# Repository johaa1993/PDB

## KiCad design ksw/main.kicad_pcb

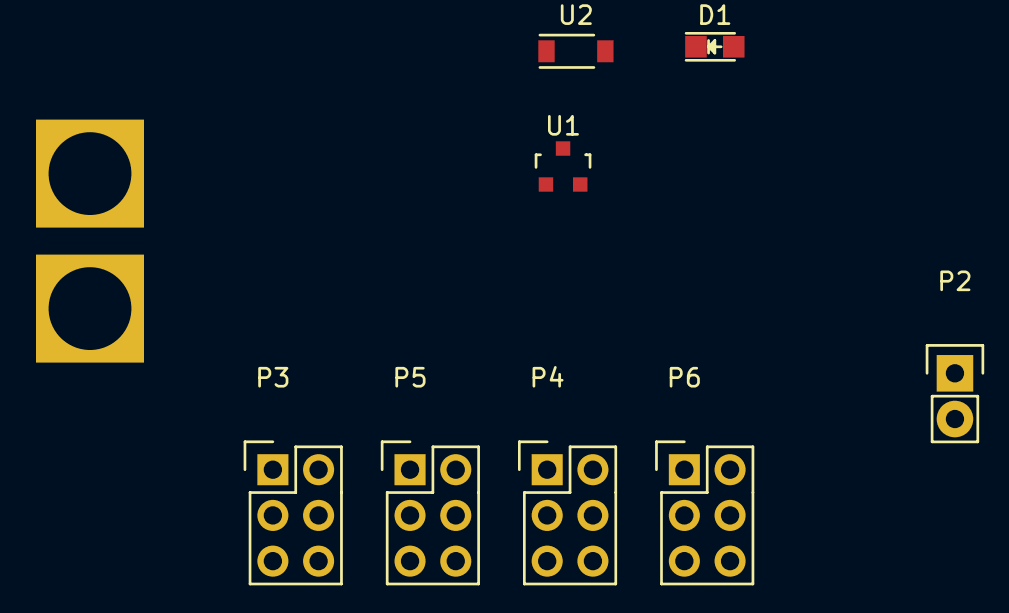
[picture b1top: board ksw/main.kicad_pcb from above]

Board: 2 copper layers, 9 parts (0 on the bottom side), 5 nets, no tracks yet.

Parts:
D1: 3.3v; LED_0805
P1: CONN_XT60; XT60
P2: CONN_01X02; Pin_Header_Straight_1x02
P3, P4, P5, P6: CONN_02X03; Pin_Header_Straight_2x03
U1: LM3480-3.3; SOT-23
U2: NSI45020AT1G; SOD-123

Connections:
+3V3: P3.6, P4.6, P5.6, P6.6, U1.1
/GND: D1.1, P1.1, P3.1, P4.1, P5.1, P6.1, U1.3
/In+: P1.2, U1.2, U2.2
unnamed: D1.2, P2.2, U2.1
unnamed: P2.1, P3.5, P4.5, P5.5, P6.5

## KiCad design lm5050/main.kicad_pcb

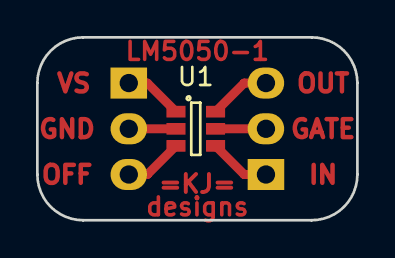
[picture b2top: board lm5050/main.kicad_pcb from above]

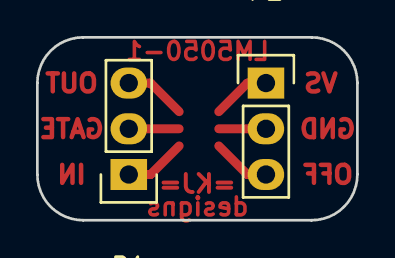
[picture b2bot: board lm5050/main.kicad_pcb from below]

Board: 2 copper layers, 17.8 x 10.2 mm, 3 parts (2 on the bottom side), 6 nets.

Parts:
P1, P2: CONN_01X03; Pin_Header_Straight_1x03
U1: LM5050; SOT-23-6

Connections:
unnamed: P1.1, U1.4
unnamed: P1.2, U1.5
unnamed: P1.3, U1.6
unnamed: P2.1, U1.1
unnamed: P2.2, U1.2
unnamed: P2.3, U1.3

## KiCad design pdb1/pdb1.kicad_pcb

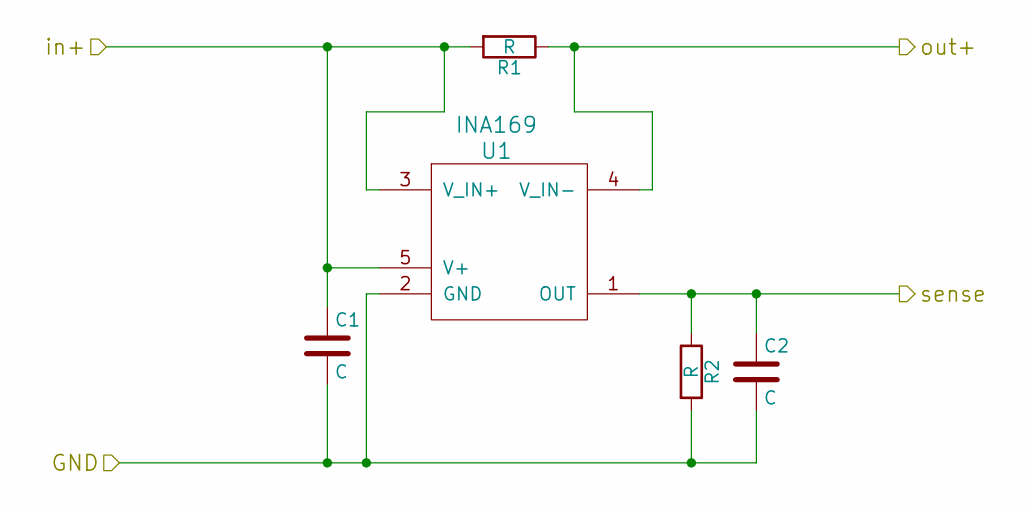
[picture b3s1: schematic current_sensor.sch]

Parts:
C1, C2: C; C_0603
R1: R; SMD_1052_Metric
R2: R; R_0603
U1: INA169; SOT-23-5

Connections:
/channel/GND: C1.2, C2.2, R2.2, U1.2 (GND); also elsewhere on the board
/channel/current_sensor/sense: C2.1, R2.1, U1.1 (OUT); also elsewhere on the board
/channel/fuse/in+: R1.1, U1.4 (V_IN-); also elsewhere on the board
/channel/in+: C1.1, R1.2, U1.3 (V_IN+), U1.5 (V+); also elsewhere on the board

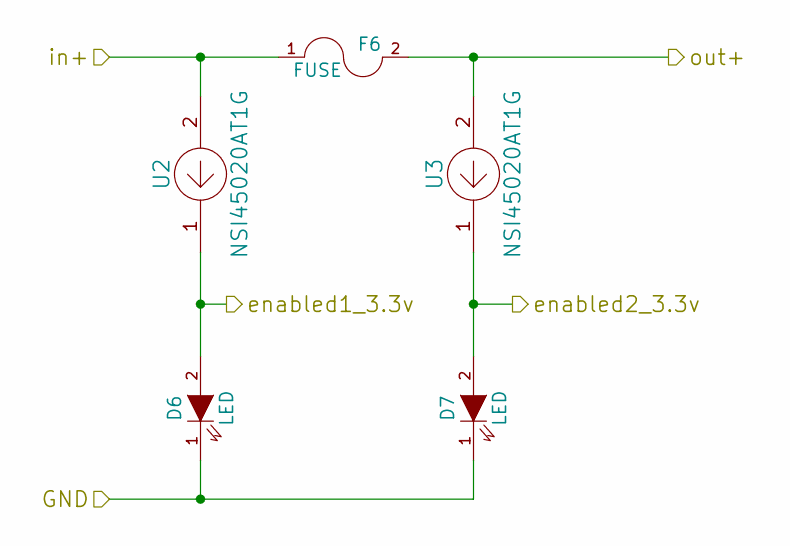
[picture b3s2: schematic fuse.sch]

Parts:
D6, D7: LED; LED_0805
F6: FUSE; Fuseholder_test
U2, U3: NSI45020AT1G; SOD-123

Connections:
/channel/GND: D6.1 (K), D7.1 (K); also elsewhere on the board
/channel/fuse/enabled1_3.3v: D6.2 (A), U2.1; also elsewhere on the board
/channel/fuse/enabled2_3.3v: D7.2 (A), U3.1; also elsewhere on the board
/channel/fuse/in+: F6.1, U2.2; also elsewhere on the board
/channel/kill_sw/in+: F6.2, U3.2; also elsewhere on the board

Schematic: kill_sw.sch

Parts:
C3: CP; C_Radial_D5_L6_P2.5
D9: LED; LED_0805
P4, P5: CONN_01X02; Pin_Header_Straight_1x02
Q2: BUK9Y4R8-60E; SOT-669_LFPAK
R3, R4: R; R_0603
U4: LM3480-3.3; SOT-23
U5: 74LVC1G08; SOT-353
U7: MIC5014; SOIC-8_3.9x4.9mm_Pitch1.27mm
U8: NSI45020AT1G; SOD-123

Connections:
/channel/GND: C3.2, D9.1 (K), R3.2, R4.2, U4.3, U5.3, U7.4 (Gnd); also elsewhere on the board
/channel/kill_sw/enable: P5.1, R3.1, U5.2; also elsewhere on the board
/channel/kill_sw/enabled2_3.3v: D9.2 (A), U8.1; also elsewhere on the board
/channel/kill_sw/in+: C3.1, Q2.5 (D), U4.2, U7.1 (V+); also elsewhere on the board
/channel/out+: Q2.1 (S), Q2.2 (S), Q2.3 (S), U7.3 (Source), U8.2; also elsewhere on the board
unnamed: P4.1, U4.1, U5.5
unnamed: P4.2, P5.2, R4.1, U5.1
unnamed: Q2.4 (G), U7.5 (Gate)
unnamed: U5.4, U7.2 (Input)

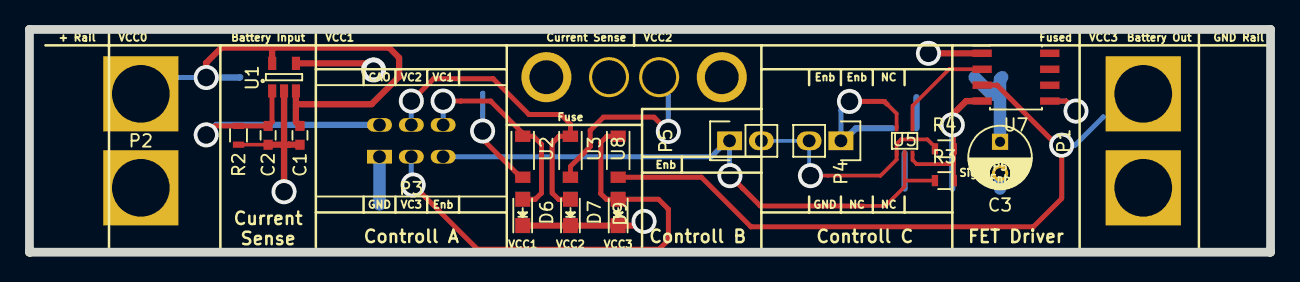
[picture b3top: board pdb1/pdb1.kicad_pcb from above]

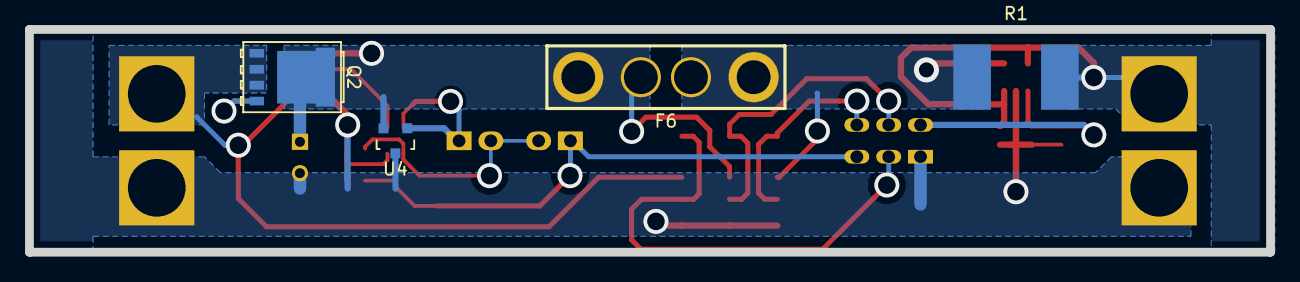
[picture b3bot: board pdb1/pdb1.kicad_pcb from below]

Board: 2 copper layers, 99.1 x 17.8 mm, 24 parts (4 on the bottom side), 14 nets.

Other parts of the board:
P1, P2: CONN_XT60; XT60
P3: CONN_02X03; Pin_Header_Straight_2x03_box

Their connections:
/channel/GND: P1.1, P2.1, P3.1; also elsewhere on the board
/channel/current_sensor/sense: P3.2; also elsewhere on the board
/channel/fuse/enabled1_3.3v: P3.6; also elsewhere on the board
/channel/fuse/enabled2_3.3v: P3.4; also elsewhere on the board
/channel/in+: P2.2; also elsewhere on the board
/channel/kill_sw/enable: P3.5; also elsewhere on the board
/channel/kill_sw/enabled2_3.3v: P3.3; also elsewhere on the board
/channel/out+: P1.2; also elsewhere on the board

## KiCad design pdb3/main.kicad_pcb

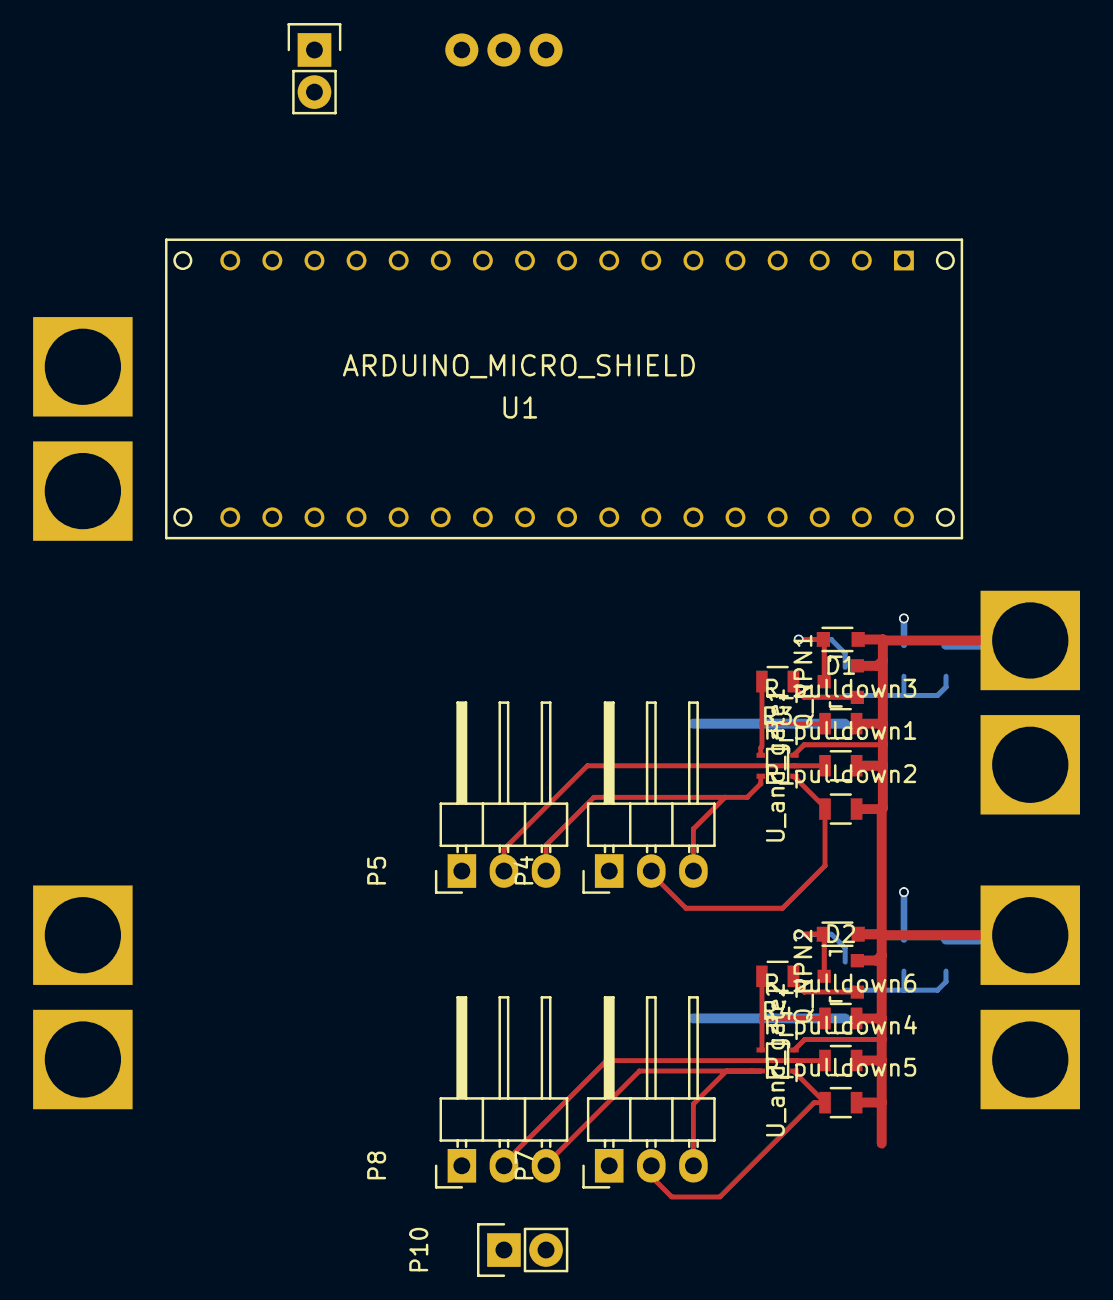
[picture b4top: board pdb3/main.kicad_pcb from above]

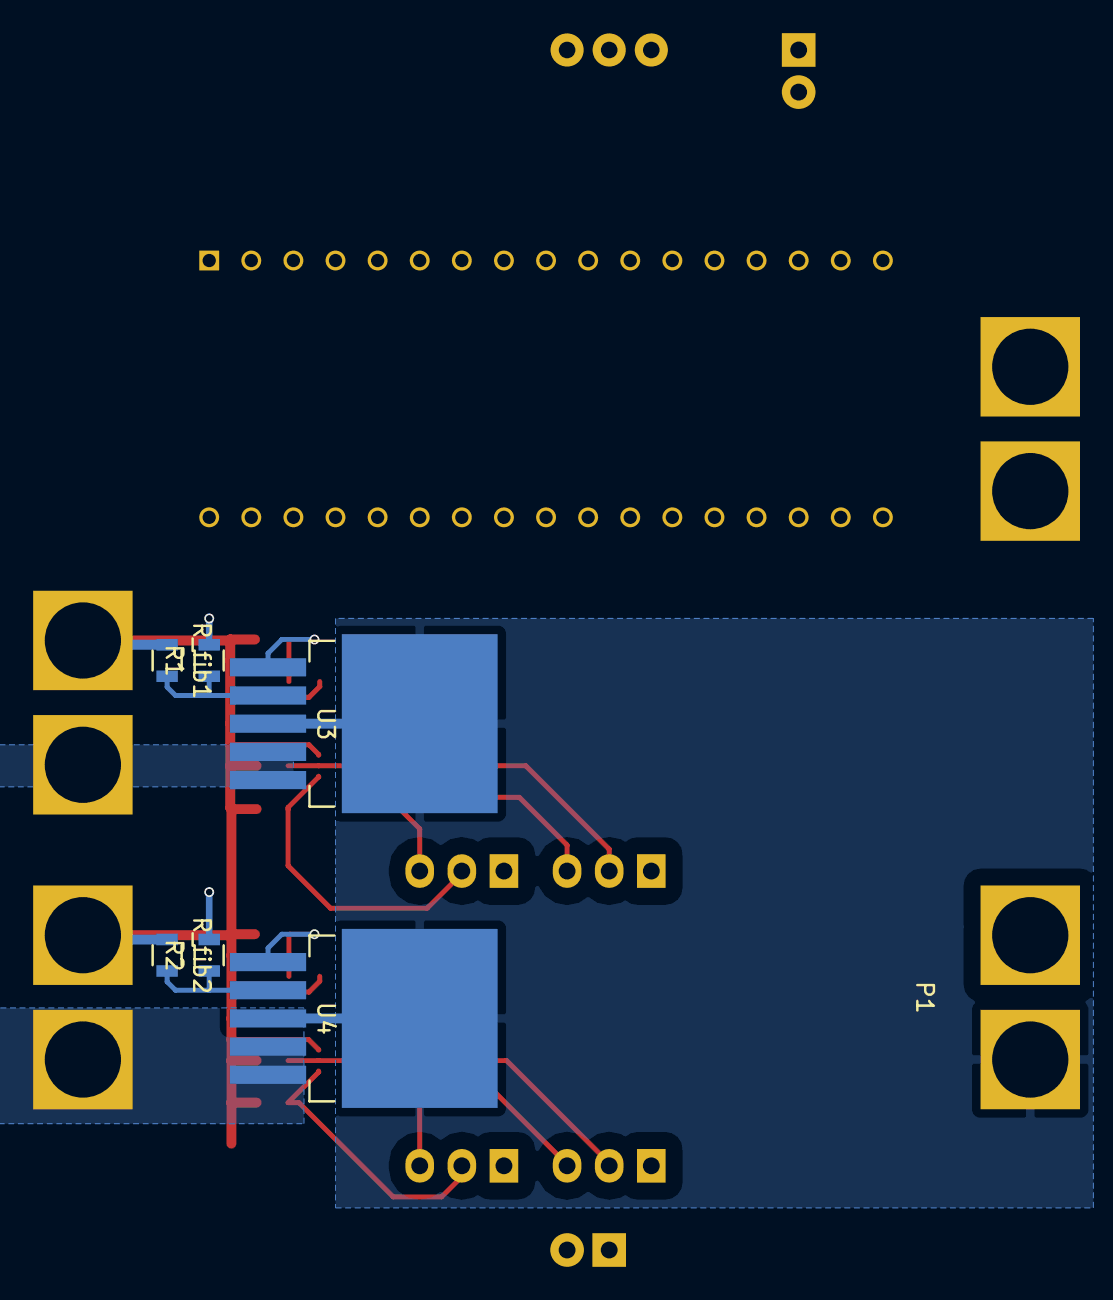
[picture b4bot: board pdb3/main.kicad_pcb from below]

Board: 4 copper layers, 32 parts (8 on the bottom side), 24 nets.

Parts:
D1, D2: D_Small; D_0805
P1, P2: CONN_XT60_Male; XT60
P3: CONN_01X02; Pin_Header_Straight_1x02
P4, P5, P7, P8: CONN_01X03; Pin_Header_Angled_1x03
P6, P9: CONN_XT60_Female; XT60
P10: CONN_01X02_Reed; Pin_Header_Straight_1x02
Q_NPN1, Q_NPN2: BC849; SOT-23
R1, R2: 10k; R_0805
R3, R4: 5k; R_0805
R_fib1, R_fib2: R; R_0805
R_pulldown1, R_pulldown2, R_pulldown3, R_pulldown4, R_pulldown5, R_pulldown6: 5k; R_0805
U1: ARDUINO_MICRO_SHIELD
U2: WPMDH1100501S; WPMDH1100xx1S
U3, U4: AUIPS7111S; TO-263-5Lead
U_and_gate1, U_and_gate2: 74LVC1G08; SOT-353

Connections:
/A0: R1.2, U1.A0
/A1: R2.2, U1.A1
/Arduino_3.3V: P4.3, P5.3, P7.3, P8.3, P10.2, U1.3.3V, U_and_gate1.5, U_and_gate2.5
/Enable0: P4.1, U1.13
/Enable1: P7.1, U1.5
/KSW1/AUIPS7111S_IN: D1.1, Q_NPN1.3, U3.1
/KSW1/Out: P6.2, U3.4, U3.5
/KSW2/AUIPS7111S_IN: D2.1, Q_NPN2.3, U4.1
/KSW2/Out: P9.2, U4.4, U4.5
GND: D1.2, D2.2, P1.2, P2.2, P3.1, P6.1, P9.1, Q_NPN1.2, Q_NPN2.2, R_fib1.1, R_fib2.1, R_pulldown1.2, R_pulldown2.2, R_pulldown3.2, R_pulldown4.2, R_pulldown5.2, R_pulldown6.2, U1.GND, U2.2, U_and_gate1.3, U_and_gate2.3
unnamed: P3.2, U2.3
unnamed: P4.2, R_pulldown2.1, U_and_gate1.1
unnamed: P5.2, R_pulldown1.1, U_and_gate1.2
unnamed: P7.2, R_pulldown5.1, U_and_gate2.1
unnamed: P8.2, R_pulldown4.1, U_and_gate2.2
unnamed: Q_NPN1.1, R3.1
unnamed: Q_NPN2.1, R4.1
unnamed: R1.1, R_fib1.2, U3.2
unnamed: R2.1, R_fib2.2, U4.2
unnamed: R3.2, R_pulldown3.1, U_and_gate1.4
unnamed: R4.2, R_pulldown6.1, U_and_gate2.4
Reed: P5.1, P8.1, P10.1
VCC_7..12V: P2.1, U1.VI
VCC_8..50V: P1.1, U3.3, U4.3

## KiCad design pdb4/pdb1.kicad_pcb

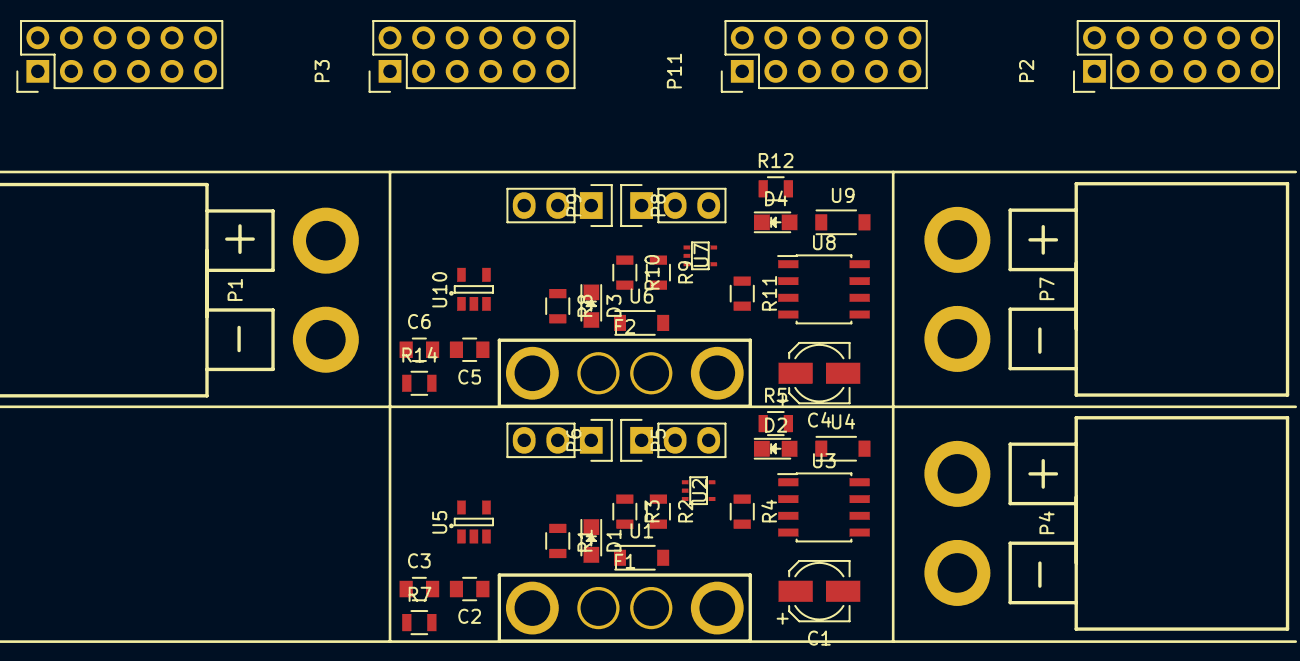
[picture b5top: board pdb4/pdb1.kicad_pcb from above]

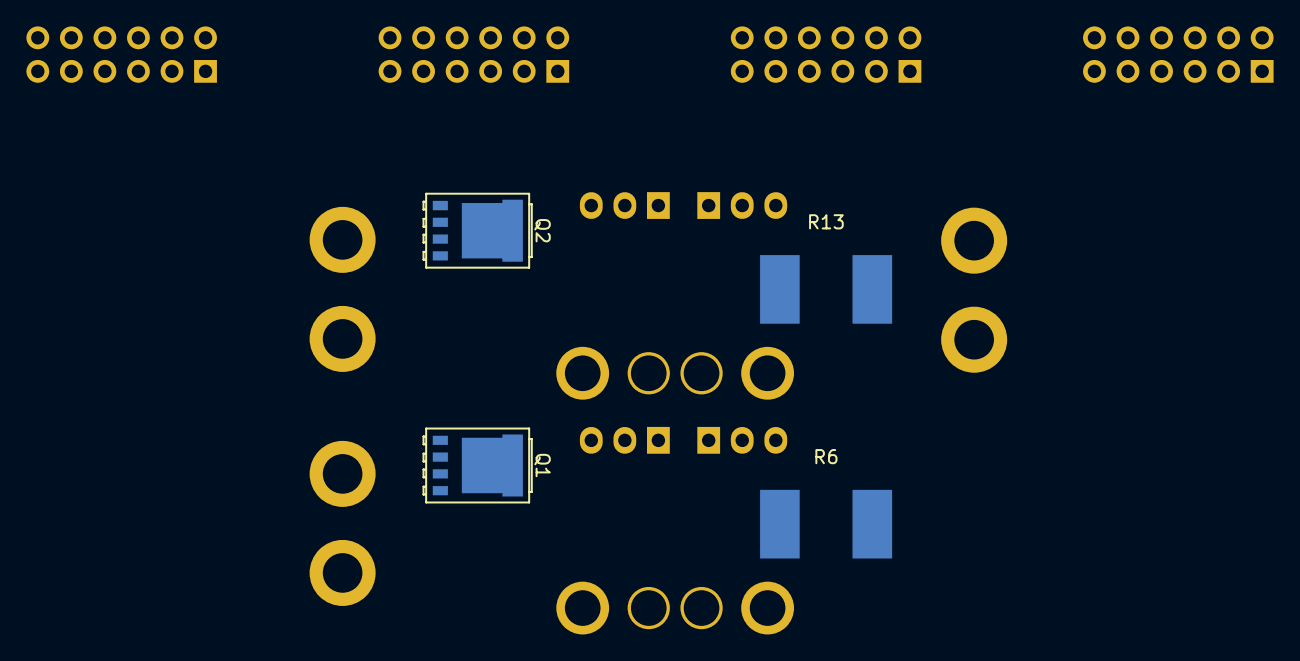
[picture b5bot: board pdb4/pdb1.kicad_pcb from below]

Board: 4 copper layers, 49 parts (4 on the bottom side), 31 nets, no tracks yet.

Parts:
C1, C4: CP; c_elec_4x4.5
C2, C3, C5, C6: C; C_0805
D1, D2, D3, D4: LED; LED_0805
F1, F2: FUSE; Fuseholder_test
P1: CONN_XT60_Male; CONN_XT60_Male1_Horizontal
P2, P3, P10, P11: CONN_02X06; Pin_Header_Straight_2x06
P4, P7: CONN_XT60_Female; CONN_XT60_Female_Horizontal
P5, P6, P8, P9: CONN_01X03; Pin_Header_Straight_1x03
Q1, Q2: BUK9Y4R8-60E; SOT-669_LFPAK
R1, R2, R3, R4, R5, R7, R8, R9, R10, R11, R12, R14: R; R_0805
R6, R13: R; SMD_1052_Metric
U1, U4, U6, U9: NSI45020AT1G; SOD-123
U2, U7: 74LVC1G08; SOT-353
U3, U8: MIC5014; SOIC-8_3.9x4.9mm_Pitch1.27mm
U5, U10: INA169; SOT-23-5

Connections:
/Current_Feedback0: C3.1, P10.3, R7.1, U5.1
/Current_Feedback1: C6.1, P10.5, R14.1, U10.1
/Enable_MCU0: P6.3, P11.3
/Enable_MCU1: P9.3, P11.5
/Enabled_Fuse0: P3.3, R1.1
/Enabled_Fuse1: P3.5, R8.1
/Enabled_SW0: P2.3, R5.1
/Enabled_SW1: P2.5, R12.1
/channel0/3.3V: P5.1, P6.1, U2.5
/channel0/Enable_Reed: P5.3, P8.3
/channel0/Power: C2.1, C5.1, P1.2, R6.2, R13.2, U5.3, U5.5, U10.3, U10.5
/channel0/fuse/in+: F1.1, R6.1, U5.4
/channel0/kill_sw/in+: C1.1, F1.2, Q1.5, U1.2, U3.1
/channel0/kill_sw/out+: P4.2, Q1.1, Q1.2, Q1.3, U3.3, U4.2
/channel1/3.3V: P8.1, P9.1, U7.5
/channel1/fuse/in+: F2.1, R13.1, U10.4
/channel1/kill_sw/in+: C4.1, F2.2, Q2.5, U6.2, U8.1
/channel1/kill_sw/out+: P7.2, Q2.1, Q2.2, Q2.3, U8.3, U9.2
GND: C1.2, C2.2, C3.2, C4.2, C5.2, C6.2, D1.1, D2.1, D3.1, D4.1, P1.1, P2.1, P3.1, P4.1, P7.1, P10.1, P11.1, R2.2, R3.2, R4.2, R7.2, R9.2, R10.2, R11.2, R14.2, U2.3, U3.4, U5.2, U7.3, U8.4, U10.2
unnamed: D1.2, R1.2, U1.1
unnamed: D2.2, R5.2, U4.1
unnamed: D3.2, R8.2, U6.1
unnamed: D4.2, R12.2, U9.1
unnamed: P5.2, R3.1, U2.1
unnamed: P6.2, R2.1, U2.2
unnamed: P8.2, R10.1, U7.1
unnamed: P9.2, R9.1, U7.2
unnamed: Q1.4, U3.5
unnamed: Q2.4, U8.5
unnamed: R4.1, U2.4, U3.2
unnamed: R11.1, U7.4, U8.2

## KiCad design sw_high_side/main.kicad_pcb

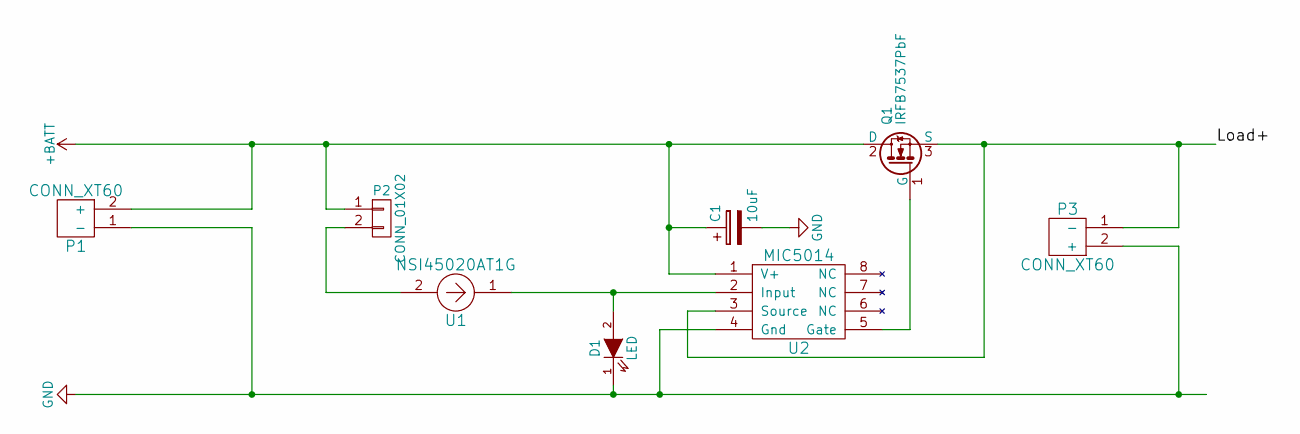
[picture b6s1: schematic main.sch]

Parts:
C1: 10uF; C_Axial_D5_L11_P18
D1: LED; LED_0805
P1, P3: CONN_XT60; XT60
P2: CONN_01X02; Pin_Header_Straight_1x02
Q1: IRFB7537PbF; TO-220_Horizontal_LargePads_HeatsinkPad
U1: NSI45020AT1G; SOD-123
U2: MIC5014; SOIC-8-N

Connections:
+BATT: C1.1, P1.2 (+), P2.1, Q1.2 (D), U2.1 (V+)
/Load+: P3.1 (-), Q1.3 (S), U2.3 (Source)
GND: C1.2, D1.1 (K), P1.1 (-), P3.2 (+), U2.4 (Gnd)
unnamed: D1.2 (A), U1.1, U2.2 (Input)
unnamed: P2.2, U1.2
unnamed: Q1.1 (G), U2.5 (Gate)

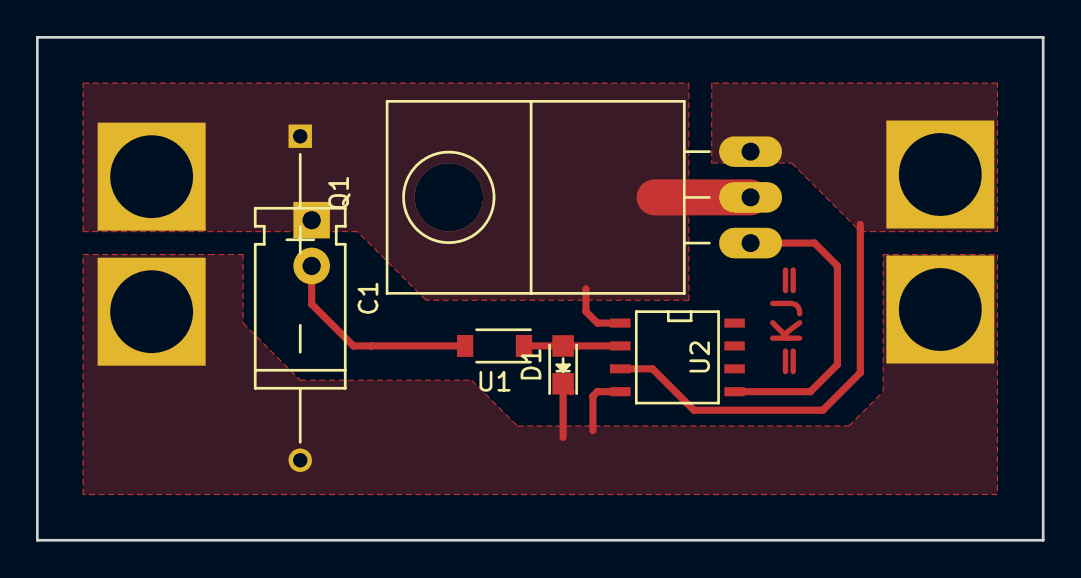
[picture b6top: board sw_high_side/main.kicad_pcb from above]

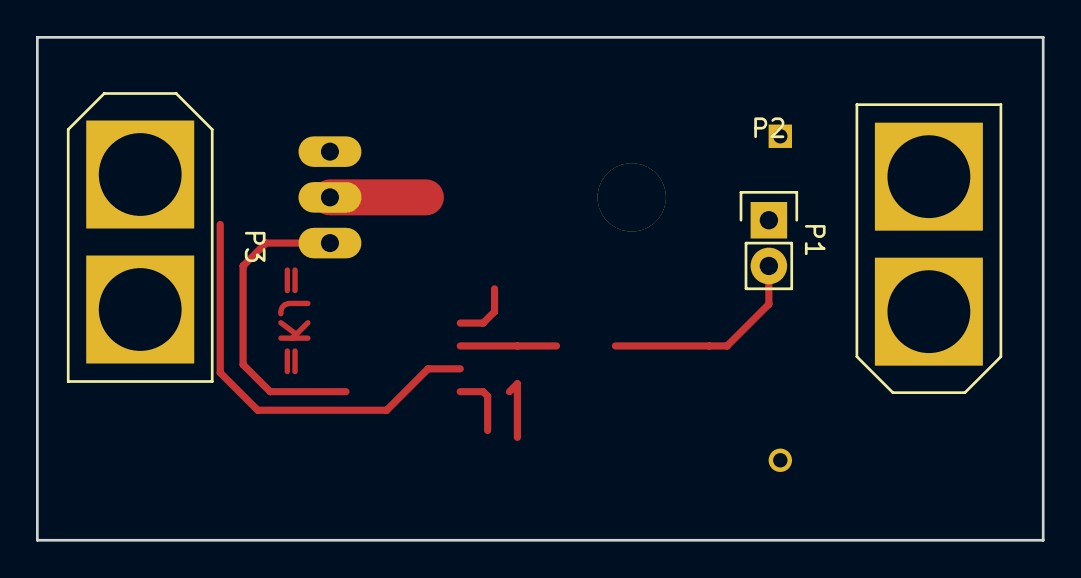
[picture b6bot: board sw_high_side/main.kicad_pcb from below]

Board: 2 copper layers, 55.9 x 27.9 mm, 8 parts (3 on the bottom side), 6 nets.

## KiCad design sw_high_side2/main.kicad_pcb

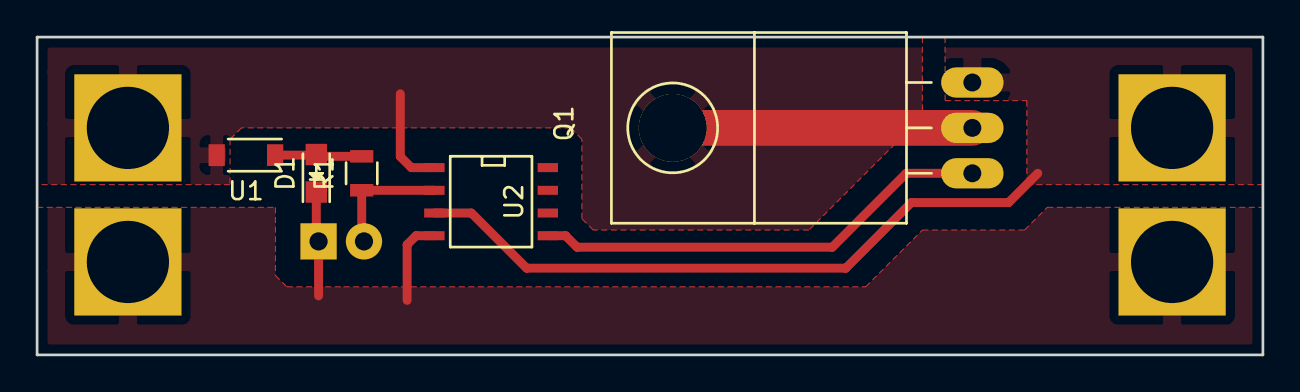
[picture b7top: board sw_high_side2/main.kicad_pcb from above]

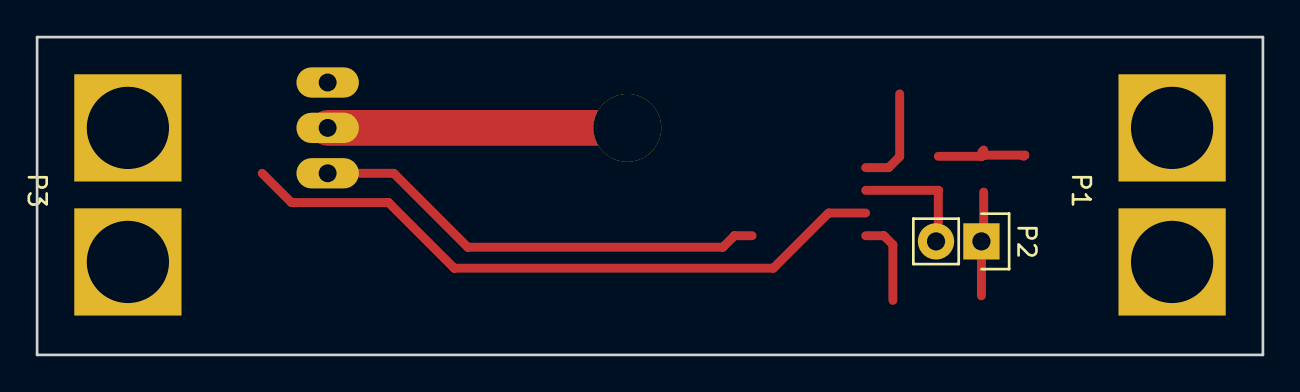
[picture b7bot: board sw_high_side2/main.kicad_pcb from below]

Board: 2 copper layers, 68.6 x 17.8 mm, 8 parts (3 on the bottom side), 6 nets.

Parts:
D1: LED; LED_0805
P1, P3: CONN_XT60; XT60
P2: CONN_01X02; Pin_Header_Straight_1x02
Q1: IRFB7537PbF; TO-220_Horizontal_LargePads_HeatsinkPad
R1: 10k; R_0805
U1: NSI45020AT1G; SOD-123
U2: MIC5014; SOIC-8-N

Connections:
/In+: P1.2, Q1.2, U1.2, U2.1
/In-: D1.1, P1.1, P2.1, P3.1, U2.4
/Out+: P3.2, Q1.3, U2.3
unnamed: D1.2, R1.2, U1.1
unnamed: P2.2, R1.1, U2.2
unnamed: Q1.1, U2.5
